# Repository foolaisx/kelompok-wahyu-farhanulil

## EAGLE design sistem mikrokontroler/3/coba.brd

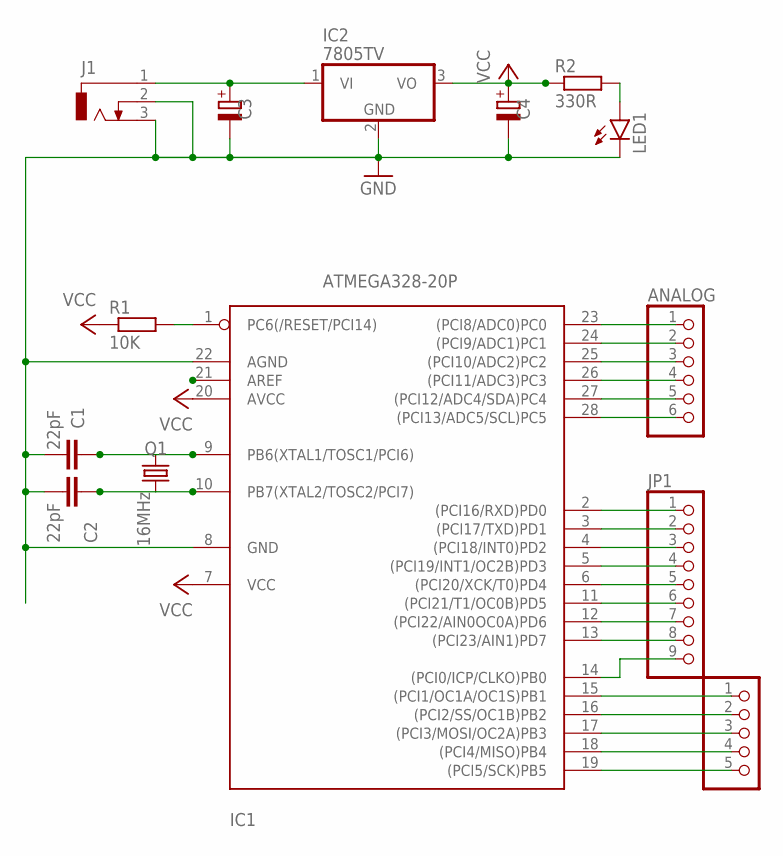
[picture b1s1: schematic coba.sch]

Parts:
ANALOG: PINHD-1X6; 1X06
C1, C2: 22pF; C025-024X044
C3, C4: CPOL-EUE2.5-6; E2,5-6
DIGITAL2: PINHD-1X5; 1X05
IC1: ATMEGA328-20P; DIL28-3
IC2: 7805TV; TO220V
J1: DCJ0303
JP1: PINHD-1X9; 1X09
LED1: LED3MM
Q1: 16MHz; HC49U70
R1: 10K; 0207/10
R2: 330R; 0207/10

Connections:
ANALOG: ANALOG.2, IC1.24 ((PCI9/ADC1)PC1)
GND: C1.2, C2.2, C3.-, C4.-, IC1.8 (GND), IC1.22 (AGND), IC2.2 (GND), J1.2, J1.3, LED1.K (C)
unnamed: IC1.1 (PC6(/RESET/PCI14)), R1.2
unnamed: C1.1, IC1.9 (PB6(XTAL1/TOSC1/PCI6)), Q1.1
unnamed: C2.1, IC1.10 (PB7(XTAL2/TOSC2/PCI7)), Q1.2
unnamed: ANALOG.1, IC1.23 ((PCI8/ADC0)PC0)
unnamed: C3.+, IC2.1 (VI), J1.1
unnamed: ANALOG.3, IC1.25 ((PCI10/ADC2)PC2)
unnamed: ANALOG.4, IC1.26 ((PCI11/ADC3)PC3)
unnamed: ANALOG.5, IC1.27 ((PCI12/ADC4/SDA)PC4)
unnamed: ANALOG.6, IC1.28 ((PCI13/ADC5/SCL)PC5)
unnamed: IC1.2 ((PCI16/RXD)PD0), JP1.1
unnamed: IC1.3 ((PCI17/TXD)PD1), JP1.2
unnamed: IC1.4 ((PCI18/INT0)PD2), JP1.3
unnamed: IC1.5 ((PCI19/INT1/OC2B)PD3), JP1.4
unnamed: IC1.6 ((PCI20/XCK/T0)PD4), JP1.5
unnamed: IC1.11 ((PCI21/T1/OC0B)PD5), JP1.6
unnamed: IC1.12 ((PCI22/AIN0OC0A)PD6), JP1.7
unnamed: IC1.13 ((PCI23/AIN1)PD7), JP1.8
unnamed: DIGITAL2.1, IC1.15 ((PCI1/OC1A/OC1S)PB1)
unnamed: DIGITAL2.2, IC1.16 ((PCI2/SS/OC1B)PB2)
unnamed: DIGITAL2.3, IC1.17 ((PCI3/MOSI/OC2A)PB3)
unnamed: DIGITAL2.4, IC1.18 ((PCI4/MISO)PB4)
unnamed: DIGITAL2.5, IC1.19 ((PCI5/SCK)PB5)
unnamed: IC1.14 ((PCI0/ICP/CLKO)PB0), JP1.9
unnamed: LED1.A, R2.2
VCC: C4.+, IC1.7 (VCC), IC1.20 (AVCC), IC1.21 (AREF), IC2.3 (VO), R1.1, R2.1

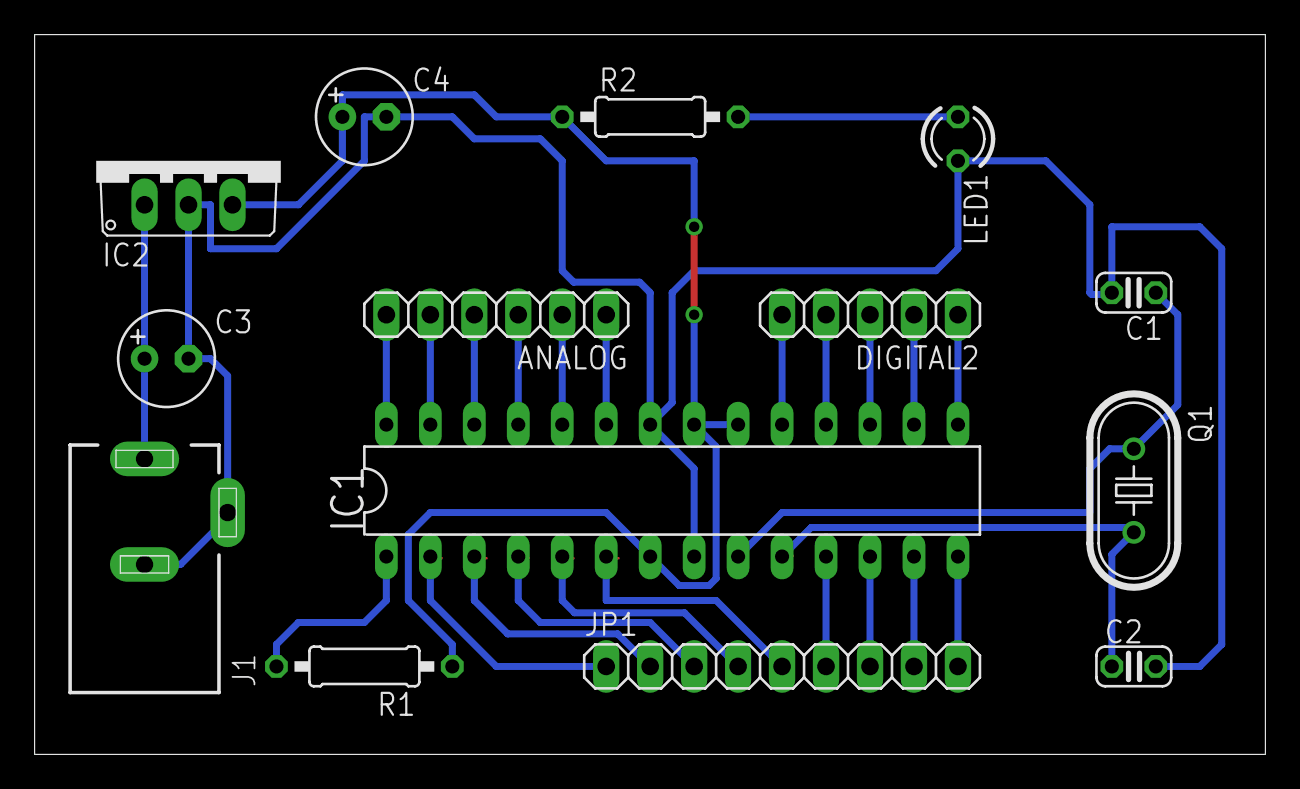
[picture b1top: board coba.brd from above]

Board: 2 copper layers, 71.1 x 41.6 mm, 14 parts (0 on the bottom side), 27 nets.

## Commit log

2021-03-22 update interface 4,sisken p,p&d
2021-03-28 mikro 5
2021-03-29 update assessment 1 interface
2021-03-29 update assessment 1 sistem kendali
2021-03-31 update mikro 6
2021-04-04 update sisken 4 & interface 7
2021-04-13 update interface mod 7,8,9
2021-04-14 update praktikum mandiri pid
2021-04-17 update interface mandiri
2021-04-22 assessment 2 interface
2021-04-26 update assess 2 sistem kendali
